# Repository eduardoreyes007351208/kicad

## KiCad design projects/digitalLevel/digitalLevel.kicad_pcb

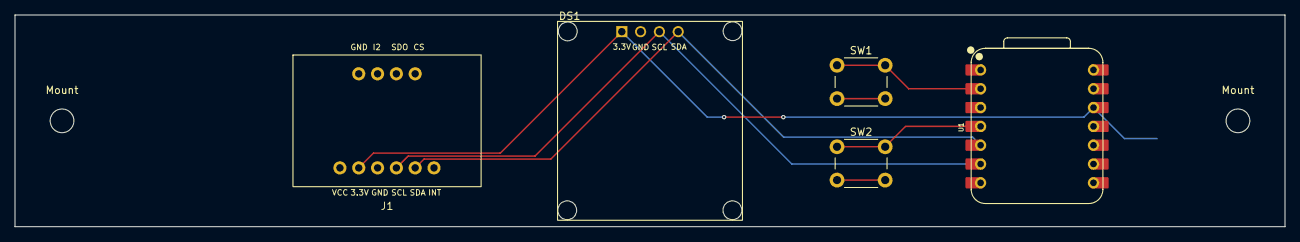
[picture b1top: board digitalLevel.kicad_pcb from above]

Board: 2 copper layers, 171.4 x 28.6 mm, 8 parts (1 on the bottom side), 6 nets.

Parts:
DS1: OLED_128X64_1.3_I2C; LCD_OLED_128X64_1.3_I2C
J1: Conn_01x04_Socket; ADXL343
Mount: MountingHole_3.2mm_M3
Mount#2: MountingHole_3.2mm_M3
SW1, SW2: SW_DIP_x02; SW_PUSH_6mm_H5mm
U1: XIAO-RP2040-DIP
U2: 2xAAABattery

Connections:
/3.3V: DS1.1 (VDD), J1.6, U1.12 (3V3), U2.1 (+)
/GND: DS1.2 (GND), J1.7, SW1.3, SW1.4, SW2.3, SW2.4, U1.13 (GND), U2.2 (-)
/PIN1: SW1.1, SW1.2, U1.2 (P27_A1_D1)
/PIN2: SW2.1, SW2.2, U1.4 (P29_A3_D3)
/SCL: DS1.3 (SCK), J1.8, U1.6 (P7_SCL_D5)
/SDA: DS1.4 (SDA), J1.9, U1.5 (P6_SDA_D4)

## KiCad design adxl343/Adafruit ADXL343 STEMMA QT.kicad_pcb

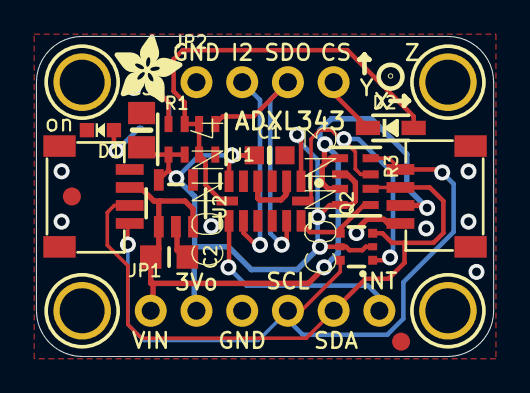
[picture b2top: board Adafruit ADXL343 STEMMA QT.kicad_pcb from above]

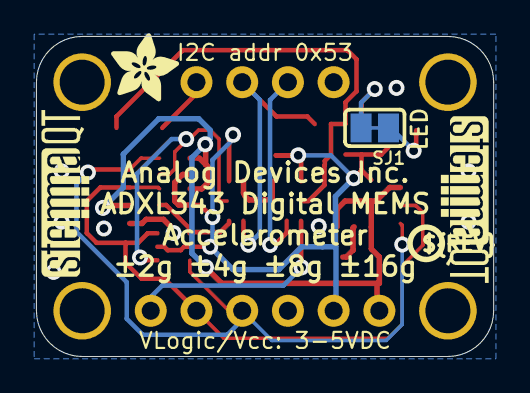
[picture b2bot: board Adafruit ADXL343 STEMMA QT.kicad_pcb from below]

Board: 2 copper layers, 25.4 x 17.8 mm, 26 parts (5 on the bottom side), 14 nets.

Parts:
C1: 0.1uF; 0603-NO
C2: 10uF; _0805MP
C3: 10uF; 0805-NO
CONN3, CONN4: STEMMA_I2C_QT; JST_SH4
D1: GREEN; CHIPLED_0603_NOOUTLINE
D2: 1N4148; SOD-323
FID3, FID4: FIDUCIAL_1MM
JP1: 1X06_ROUND_70
JP2: 1X04_ROUND
Q2: BSS138; SOT363
R1, R3: 10K; RESPACK_4X0603
SJ1: SOLDERJUMPER_CLOSEDWIRE
U1: ADXL343; LGA14
U2: AP2112K-3.3; SOT23-5
U$1, U$17, U$19, U$21: MOUNTINGHOLE2.5; MOUNTINGHOLE_2.5_PLATED
U$4, U$11: ADAFRUIT_3.5MM
U$25: PCBFEAT-REV-040
U$30, U$31: STEMMAQT

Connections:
3.3V: C1.1, C3.1, JP1.2, Q2.2, Q2.5, R1.1, R1.2, R3.2, R3.4, U1.1, U1.6, U2.5
CS: D2.C, JP2.4
CS_3V: D2.A, R1.3, R1.6, R1.7, U1.7
GND: C1.2, C2.2, C3.2, CONN3.1, CONN3.MT1, CONN3.MT2, CONN4.1, CONN4.MT1, CONN4.MT2, D1.C, JP1.3, JP2.1, R1.4, U1.2, U1.4, U1.5, U2.2
INT1: JP1.6, U1.8
INT2: JP2.2, U1.9
unnamed: R1.8, SJ1.2
unnamed: D1.A, SJ1.1
SCL: CONN3.4, CONN4.4, JP1.4, Q2.6, R3.8
SCL_3V: Q2.1, R3.7, U1.14
SDA/SDIO: CONN3.3, CONN4.3, JP1.5, Q2.3, R3.6
SDA/SDIO_3V: Q2.4, R3.5, U1.13
SDO: JP2.3, R1.5, U1.12
VCC: C2.1, CONN3.2, CONN4.2, JP1.1, R3.1, R3.3, U2.1, U2.3

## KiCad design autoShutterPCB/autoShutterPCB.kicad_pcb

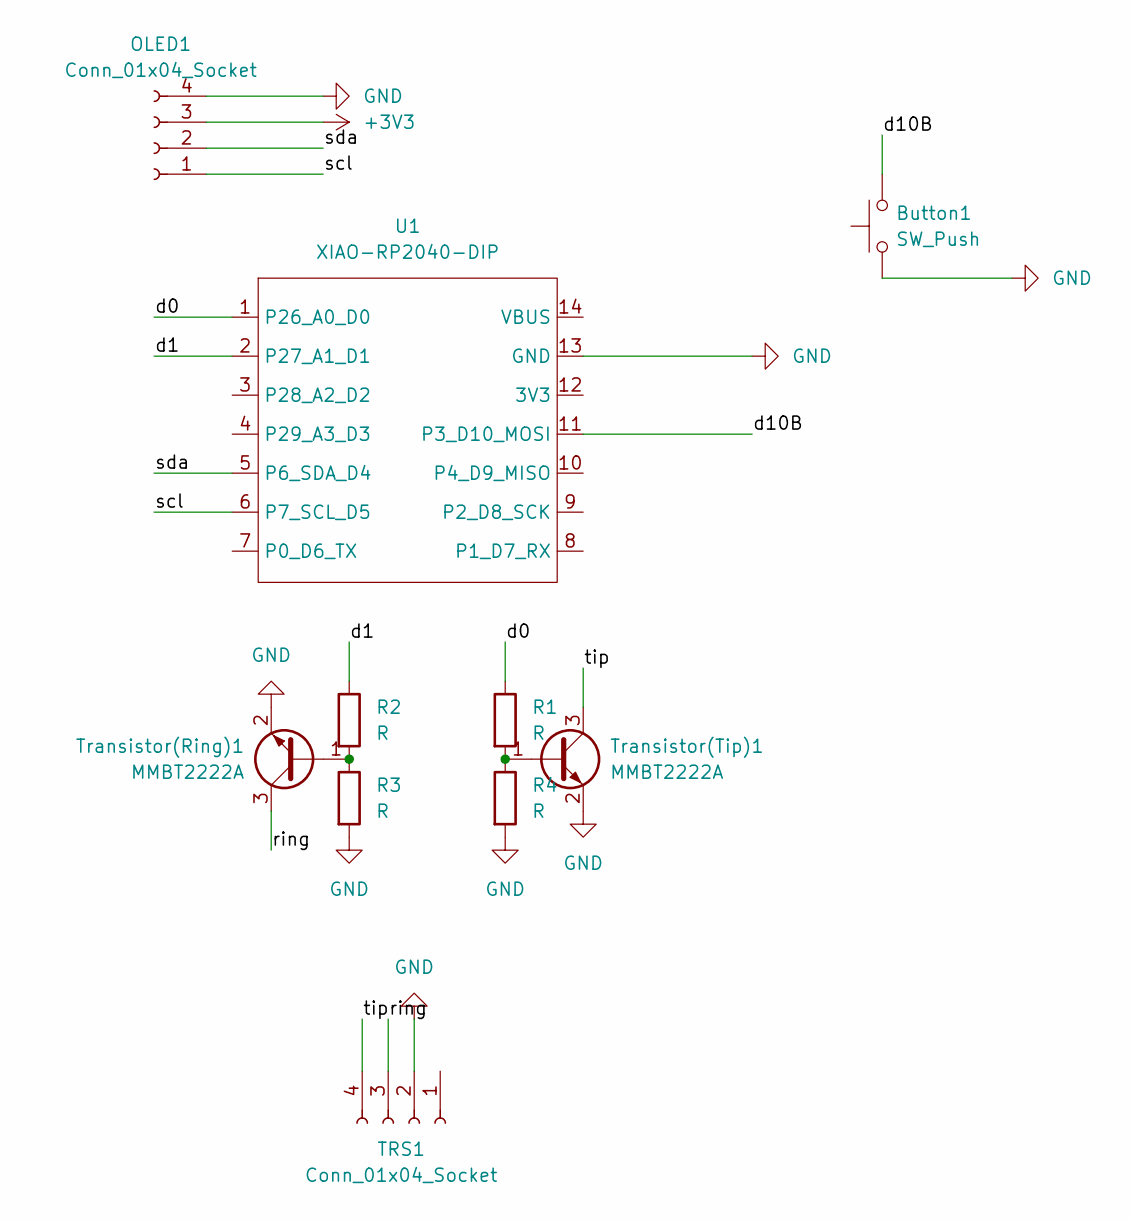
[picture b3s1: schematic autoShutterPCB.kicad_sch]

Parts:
Button1: SW_Push; SW_PUSH_6mm
OLED1: Conn_01x04_Socket; FanPinHeader_1x04_P2.54mm_Vertical
R1, R2, R3, R4: R; R_Axial_DIN0207_L6.3mm_D2.5mm_P10.16mm_Horizontal
TRS1: Conn_01x04_Socket; TRS_SMD
Transistor(Ring)1: MMBT2222A; SOT-23
Transistor(Tip)1: MMBT2222A; SOT-23
U1: XIAO-RP2040-DIP

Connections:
/3.3: OLED1.3, U1.12 (3V3)
/d0: R1.1, U1.1 (P26_A0_D0)
/d1: R2.1, U1.2 (P27_A1_D1)
/d10B: Button1.2, U1.11 (P3_D10_MOSI)
/ring: TRS1.3, Transistor(Ring)1.3 (C)
/scl: OLED1.1, U1.6 (P7_SCL_D5)
/sda: OLED1.2, U1.5 (P6_SDA_D4)
/tip: TRS1.4, Transistor(Tip)1.3 (C)
GND: Button1.1, OLED1.4, R3.2, R4.2, TRS1.2, Transistor(Ring)1.2 (E), Transistor(Tip)1.2 (E), U1.13 (GND)
unnamed: R2.2, R3.1, Transistor(Ring)1.1 (B)
unnamed: R1.2, R4.1, Transistor(Tip)1.1 (B)

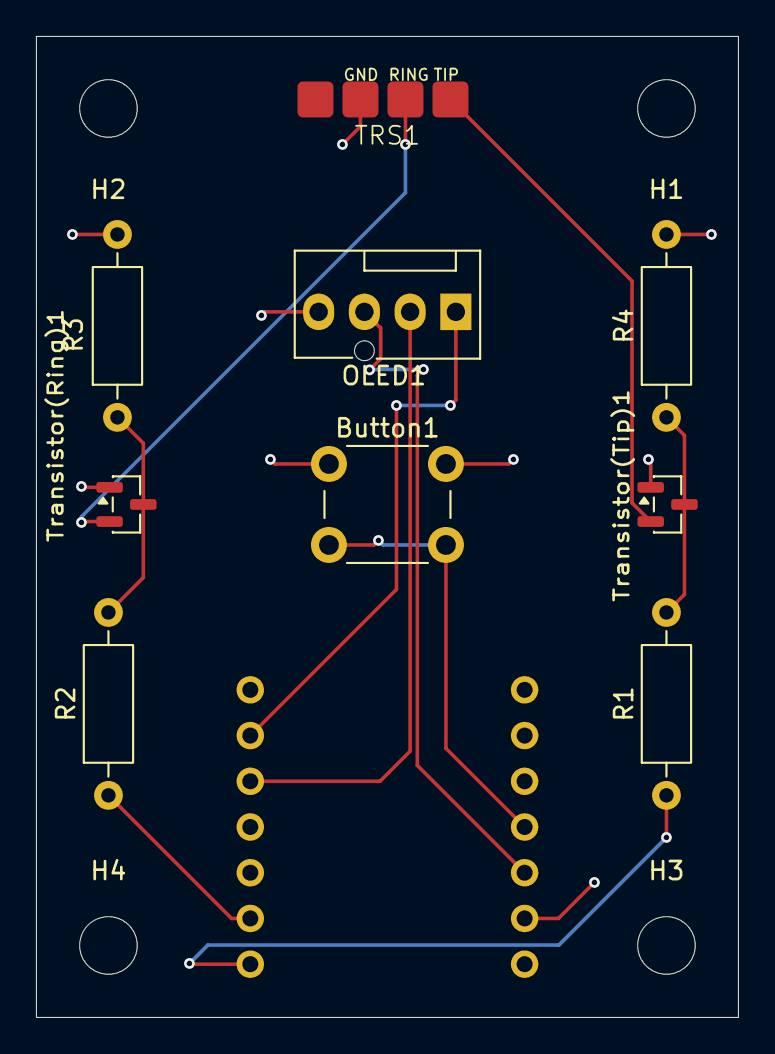
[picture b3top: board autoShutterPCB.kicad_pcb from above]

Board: 2 copper layers, 39.0 x 54.5 mm, 14 parts (1 on the bottom side), 11 nets.

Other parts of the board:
H1, H2, H3, H4: MountingHole; MountingHole_3.2mm_M3

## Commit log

2026-03-21 ignore VS Code local history folders
2026-03-21 feat: Add projects from kicad
2026-03-22 feat: Finish pcb, going to check how much it would cost
2026-03-22 feat: Correct dir for gerber files
2026-03-22 Fix: Fix silkscreen for transistor
2026-03-23 feat: Add mounting holes to design
2026-03-31 feat: Add digitalLevel dir
2026-03-31 remove tracked files that should be ignored
2026-03-31 feat: Add adxl 3d model and footprint
2026-03-31 feat: Add oled files
2026-03-31 feat: Fix path for footprints
2026-03-31 feat: Add new ssd1306 oled step
2026-03-31 feat: Add Xiao Model and start schematic
2026-04-02 feat: Fix PCB size and export Gerber
    - Changed the size of the digital level
    pcb to be 6.75"x1.125" from 8.75"x1.125".
    - Generate Gerber files for the board
    to get manufactured
    - Generate 3D .step model to model
    case around
